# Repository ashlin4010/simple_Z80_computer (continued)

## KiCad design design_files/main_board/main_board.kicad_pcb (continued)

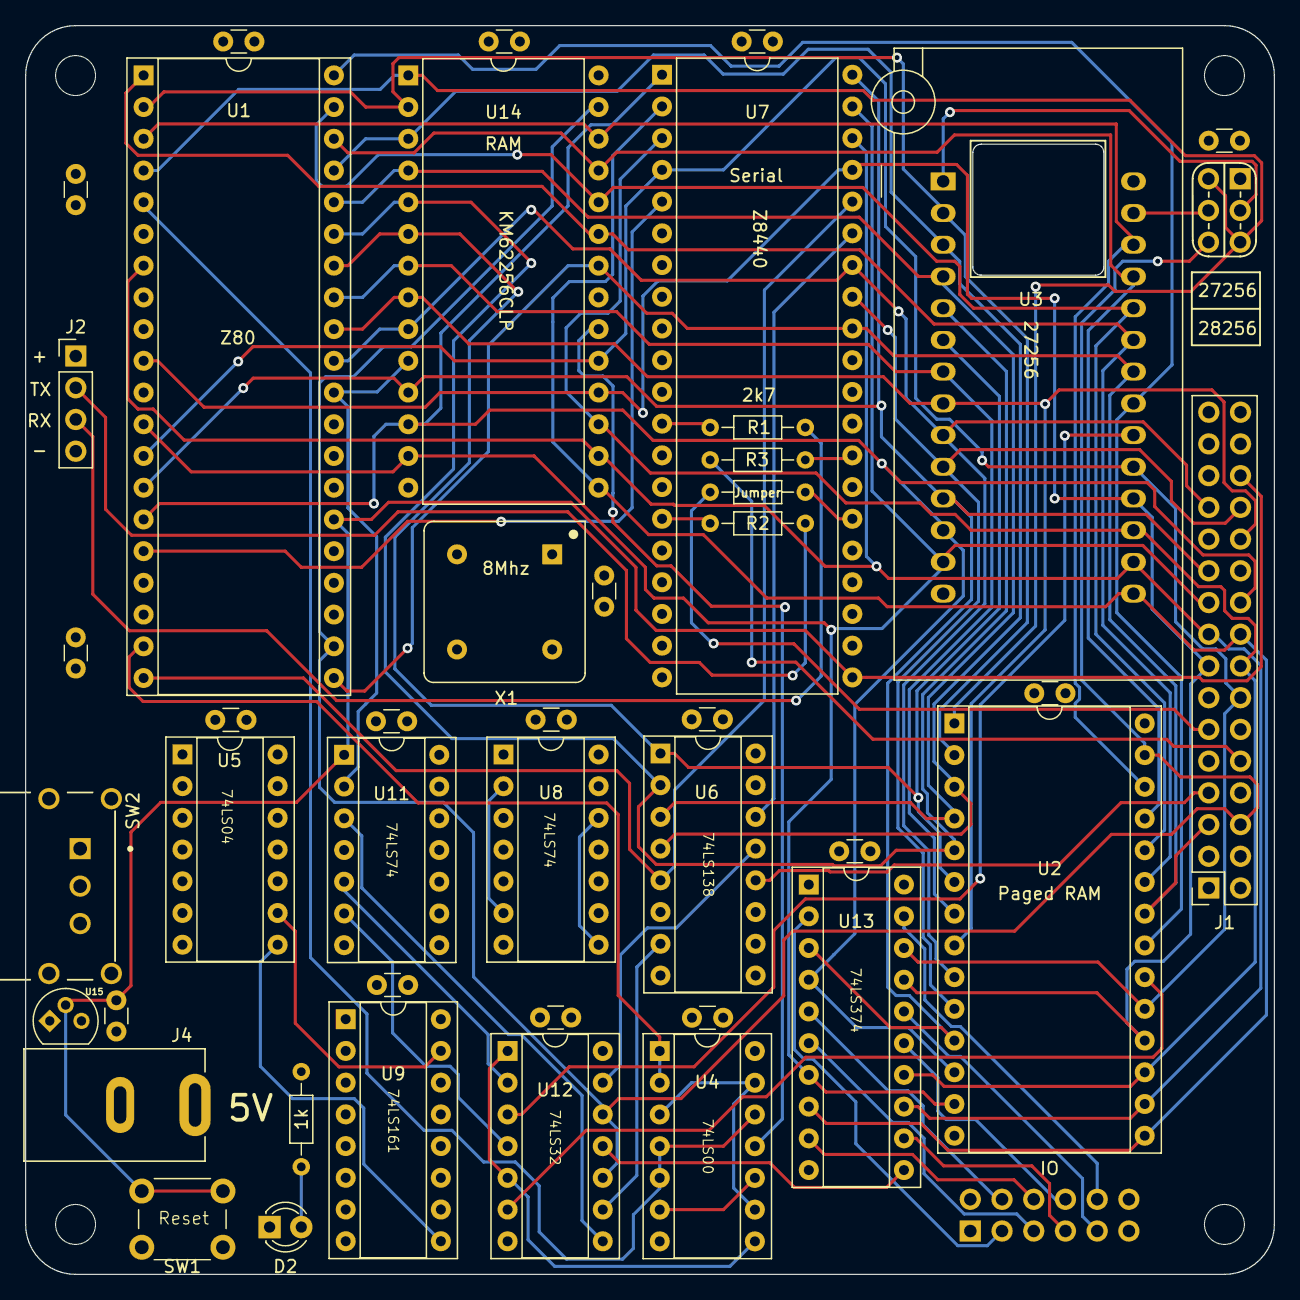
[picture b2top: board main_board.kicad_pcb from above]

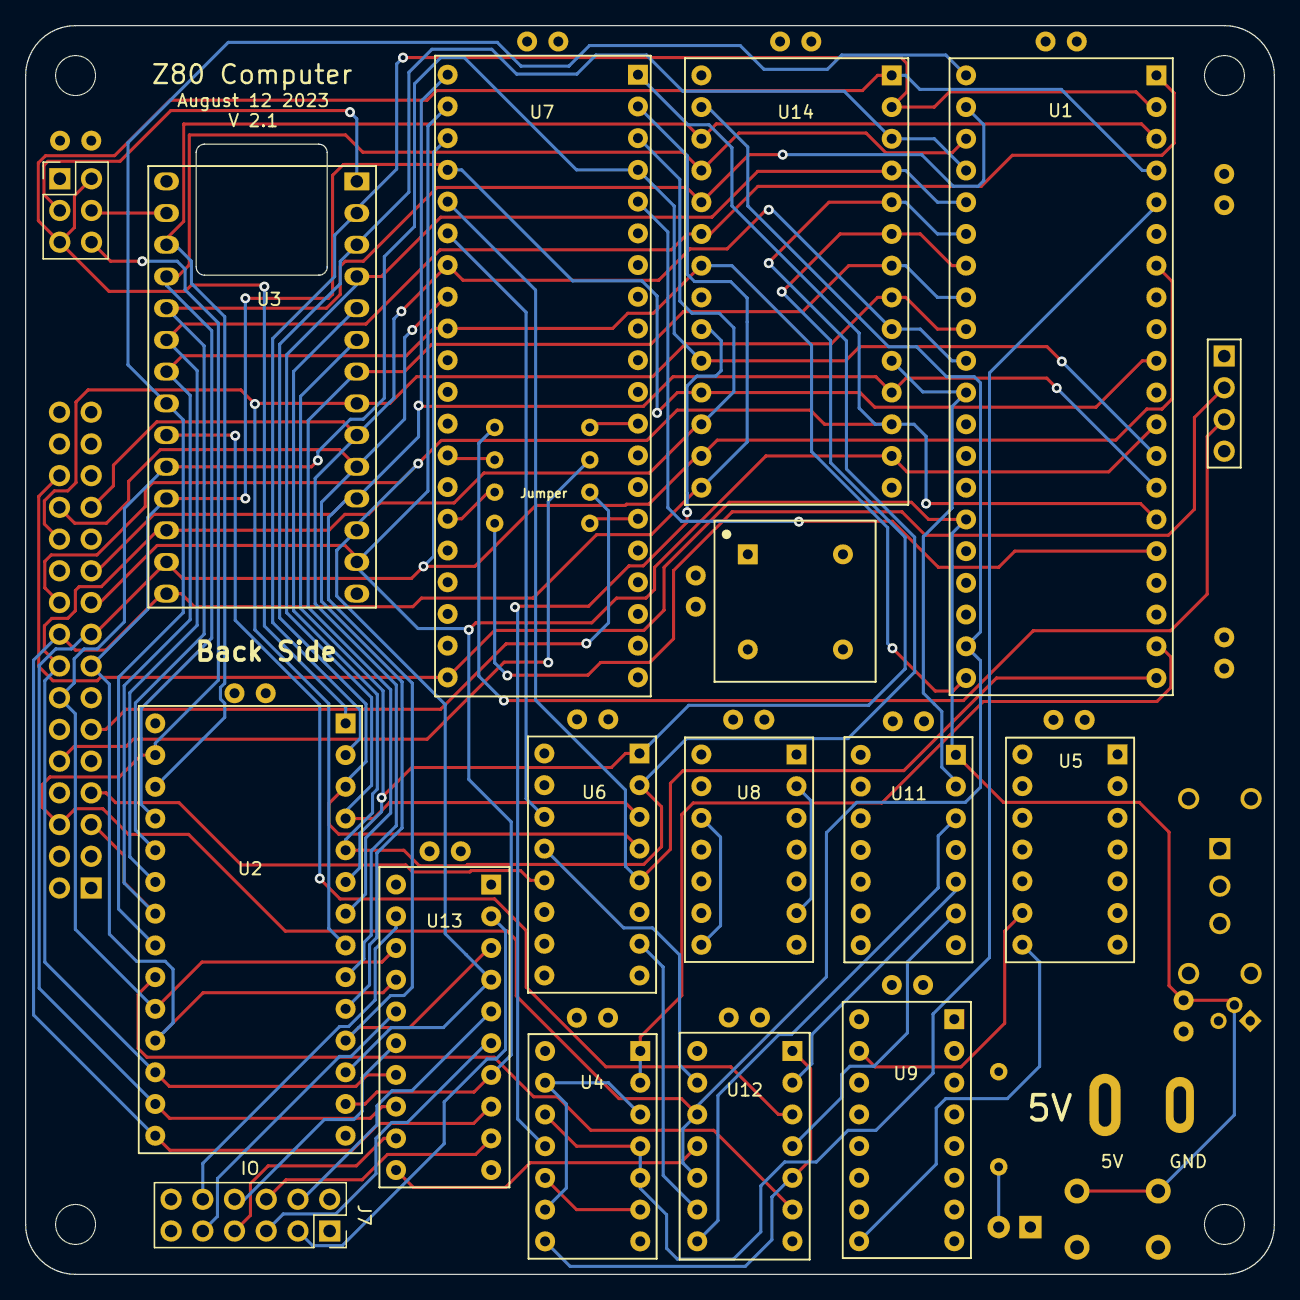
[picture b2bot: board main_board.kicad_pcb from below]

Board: 4 copper layers, 100.0 x 100.0 mm, 49 parts (2 on the bottom side), 75 nets.

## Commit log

2023-12-16 Added Kicad files
2023-12-16 Start on README
2023-12-16 More README
2023-12-17 Add some example code
2023-12-17 Added pi install instructions
2023-12-19 Added jumper settings in README
2023-12-19 Added BOM
2023-12-28 Fixed UART init Started on serial boot loader Experimenting with libraries Started on boot loader server
2023-12-30 Added Serial Bootloader
